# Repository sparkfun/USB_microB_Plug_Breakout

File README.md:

SparkFun USB MicroB Plug Breakout
========================================

[*SparkFun USB MicroB Plug Breakout (BOB-10031)*](https://www.sparkfun.com/products/10031)

We have no idea what USB device you are hooking up to, but if you want to access the microUSB port on something, you might want this. 
We broke out all 5 pins with a vertical microUSB connector for your prototyping needs.

Repository Contents
-------------------

* **/Hardware** - Eagle design files (.brd, .sch)
* **/Production** - Production panel files (.brd)

Documentation
--------------
* **[SparkFun Fritzing repo](https://github.com/sparkfun/Fritzing_Parts)** - Fritzing diagrams for SparkFun products.
* **[SparkFun 3D Model repo](https://github.com/sparkfun/3D_Models)** - 3D models of SparkFun products. 

Version History
---------------
* [v13](https://github.com/sparkfun/USB_microB_Plug_Breakout/v13) - Version 1.3. QC updates to improve manufacturing. Currently live. 
* [v12](https://github.com/sparkfun/USB_microB_Plug_Breakout/v12) - Version 1.2. Retired. 

License Information
-------------------

This product is _**open source**_! 

Please review the LICENSE.md file for license information. 

If you have any questions or concerns on licensing, please contact techsupport@sparkfun.com.

Distributed as-is; no warranty is given.

- Your friends at SparkFun.

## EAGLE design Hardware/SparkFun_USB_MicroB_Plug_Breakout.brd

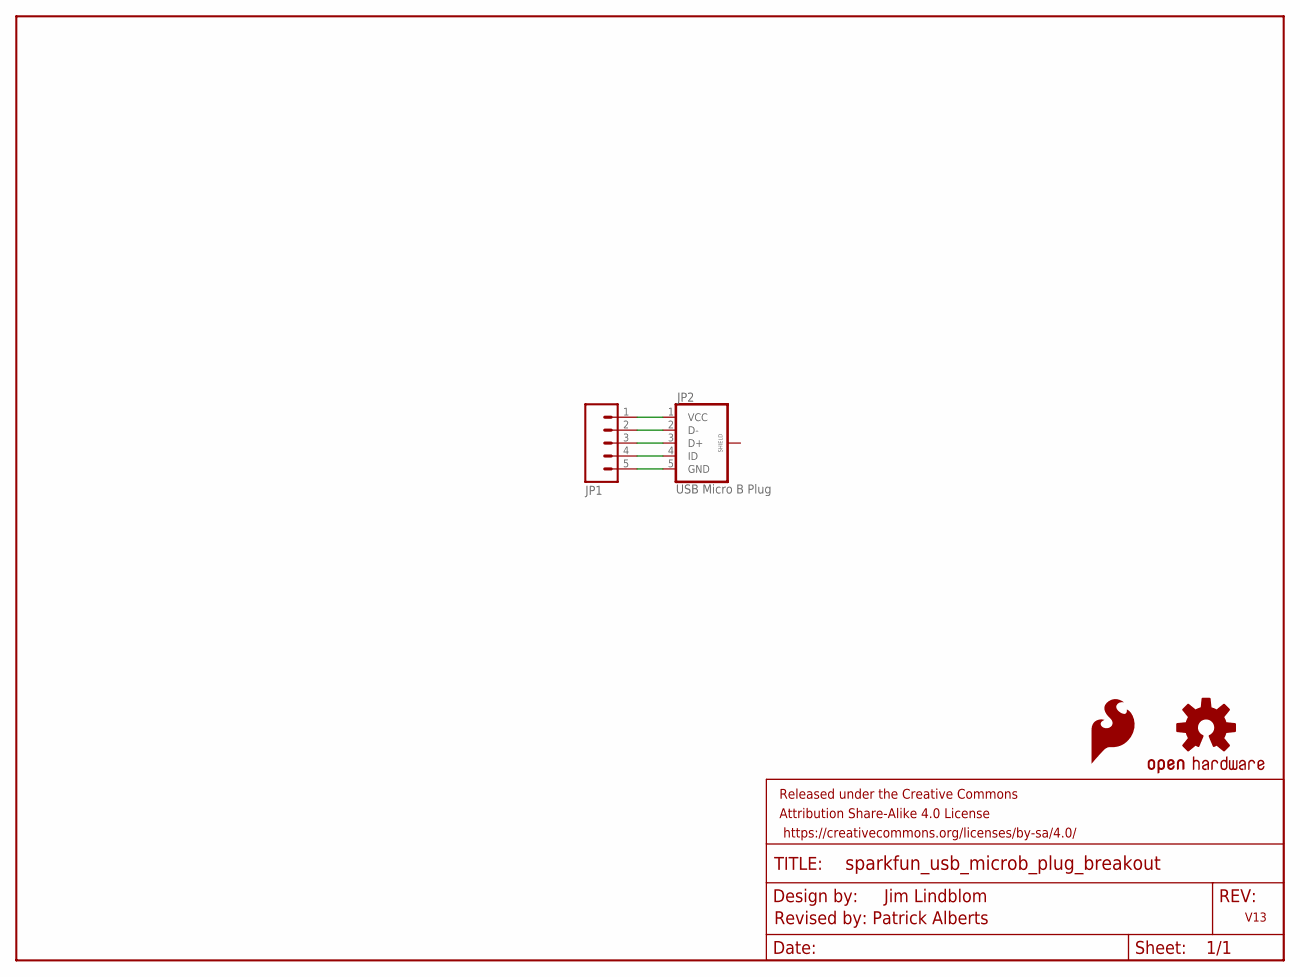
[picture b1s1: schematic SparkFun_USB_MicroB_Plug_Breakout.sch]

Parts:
FRAME1: FRAME-LETTER; CREATIVE_COMMONS
JP1: M05PTH; 1X05
JP2: USB Micro B Plug; MICRO-B-SMT
LOGO1: OSHW-LOGOS; OSHW-LOGO-S
LOGO2: SFE_LOGO_FLAME.1_INCH; SFE_LOGO_FLAME_.1

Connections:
unnamed: JP1.1, JP2.1 (VCC)
unnamed: JP1.2, JP2.2 (D-)
unnamed: JP1.3, JP2.3 (D+)
unnamed: JP1.4, JP2.4 (ID)
unnamed: JP1.5, JP2.5 (GND)

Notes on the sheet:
V13
Revised by: Patrick Alberts
Jim Lindblom

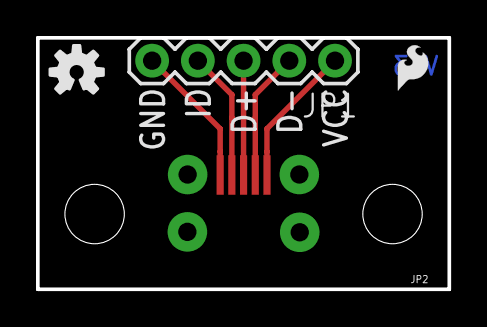
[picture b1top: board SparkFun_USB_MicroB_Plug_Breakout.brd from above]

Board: 2 copper layers, 22.9 x 14.0 mm, 5 parts (0 on the bottom side), 5 nets.

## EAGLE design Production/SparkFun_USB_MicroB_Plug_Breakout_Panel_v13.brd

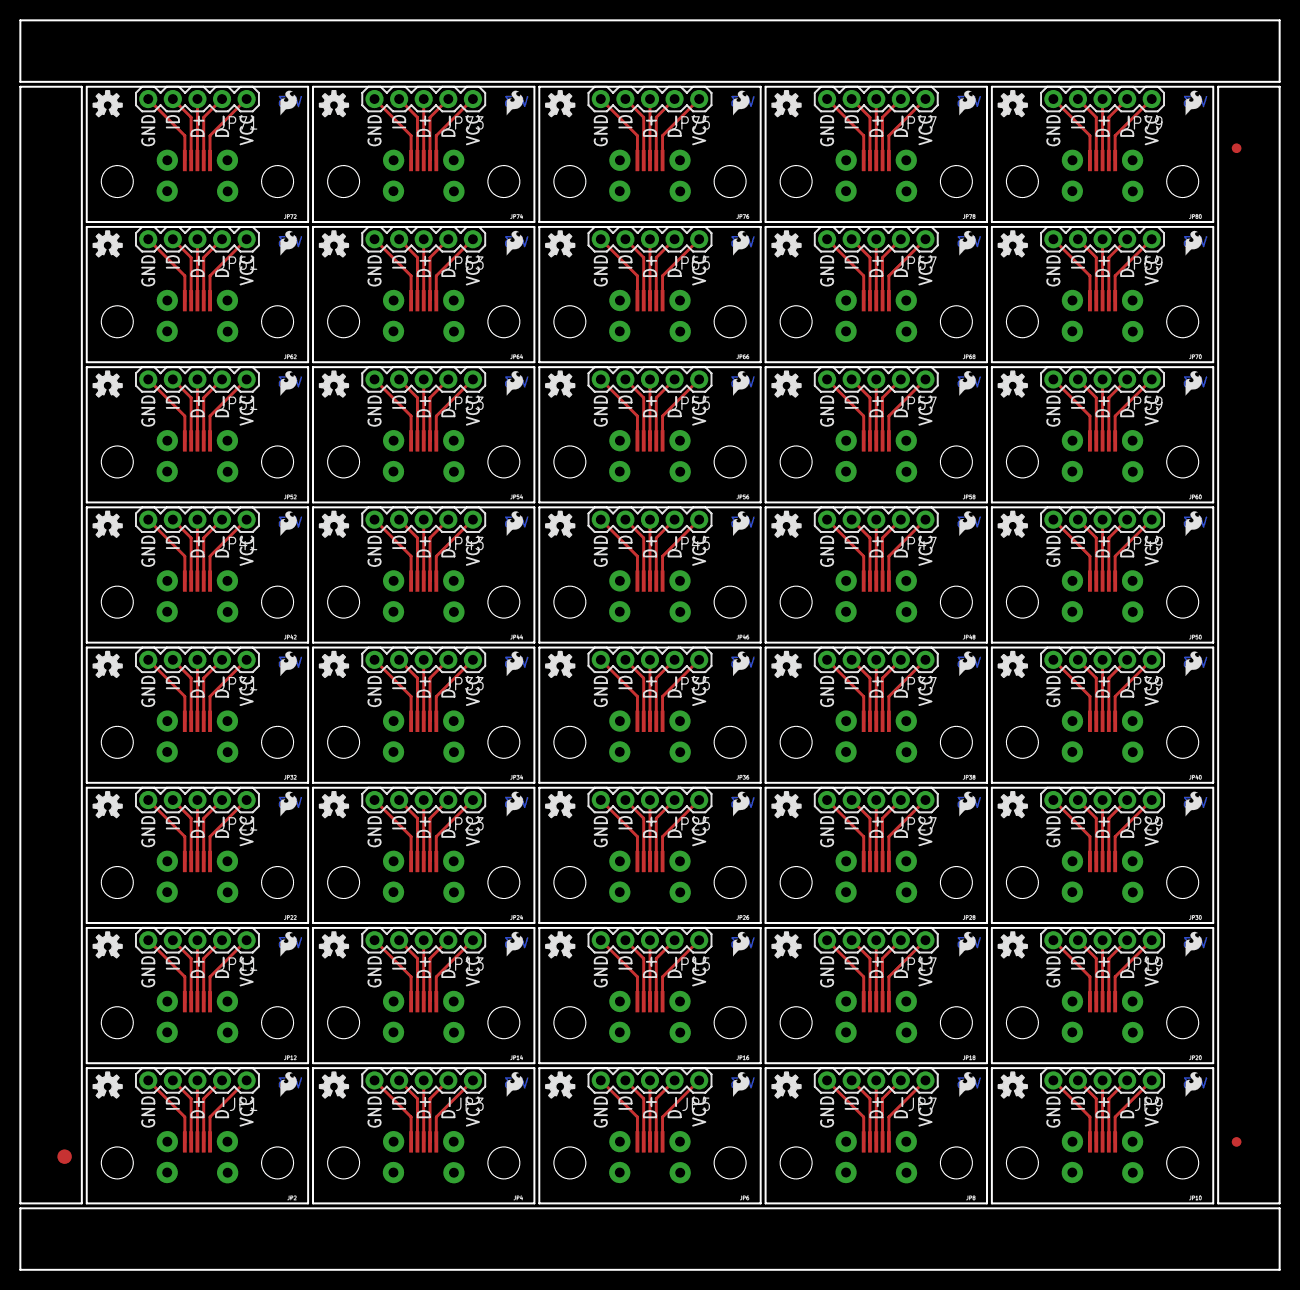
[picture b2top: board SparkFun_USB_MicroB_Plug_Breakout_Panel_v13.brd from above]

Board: 2 copper layers, 130.0 x 129.0 mm, 163 parts (0 on the bottom side), 200 nets.

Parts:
E$1: FIDUCIAL-1.5X3
E$4, E$5: FIDUCIAL-1X2
JP1, JP3, JP5, JP7, JP9, JP11, JP13, JP15, JP17, JP19, JP21, JP23, JP25, JP27, JP29, JP31, JP33, JP35, JP37, JP39, JP41, JP43, JP45, JP47, JP49, JP51, JP53, JP55, JP57, JP59, JP61, JP63, JP65, JP67, JP69, JP71, JP73, JP75, JP77, JP79: 1X05
JP2, JP4, JP6, JP8, JP10, JP12, JP14, JP16, JP18, JP20, JP22, JP24, JP26, JP28, JP30, JP32, JP34, JP36, JP38, JP40, JP42, JP44, JP46, JP48, JP50, JP52, JP54, JP56, JP58, JP60, JP62, JP64, JP66, JP68, JP70, JP72, JP74, JP76, JP78, JP80: USB Micro B Plug; MICRO-B-SMT
LOGO1, LOGO3, LOGO5, LOGO7, LOGO9, LOGO11, LOGO13, LOGO15, LOGO17, LOGO19, LOGO21, LOGO23, LOGO25, LOGO27, LOGO29, LOGO31, LOGO33, LOGO35, LOGO37, LOGO39, LOGO41, LOGO43, LOGO45, LOGO47, LOGO49, LOGO51, LOGO53, LOGO55, LOGO57, LOGO59, LOGO61, LOGO63, LOGO65, LOGO67, LOGO69, LOGO71, LOGO73, LOGO75, LOGO77, LOGO79: OSHW-LOGOS; OSHW-LOGO-S
LOGO2, LOGO4, LOGO6, LOGO8, LOGO10, LOGO12, LOGO14, LOGO16, LOGO18, LOGO20, LOGO22, LOGO24, LOGO26, LOGO28, LOGO30, LOGO32, LOGO34, LOGO36, LOGO38, LOGO40, LOGO42, LOGO44, LOGO46, LOGO48, LOGO50, LOGO52, LOGO54, LOGO56, LOGO58, LOGO60, LOGO62, LOGO64, LOGO66, LOGO68, LOGO70, LOGO72, LOGO74, LOGO76, LOGO78, LOGO80: SFE_LOGO_FLAME.1_INCH; SFE_LOGO_FLAME_.1

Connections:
unnamed: JP1.1, JP2.1
unnamed: JP1.2, JP2.2
unnamed: JP1.3, JP2.3
unnamed: JP1.4, JP2.4
unnamed: JP1.5, JP2.5
unnamed: JP3.1, JP4.1
unnamed: JP3.2, JP4.2
unnamed: JP3.3, JP4.3
unnamed: JP3.4, JP4.4
unnamed: JP3.5, JP4.5
unnamed: JP5.1, JP6.1
unnamed: JP5.2, JP6.2
unnamed: JP5.3, JP6.3
unnamed: JP5.4, JP6.4
unnamed: JP5.5, JP6.5
unnamed: JP7.1, JP8.1
unnamed: JP7.2, JP8.2
unnamed: JP7.3, JP8.3
unnamed: JP7.4, JP8.4
unnamed: JP7.5, JP8.5
unnamed: JP9.1, JP10.1
unnamed: JP9.2, JP10.2
unnamed: JP9.3, JP10.3
unnamed: JP9.4, JP10.4
unnamed: JP9.5, JP10.5
unnamed: JP11.1, JP12.1
unnamed: JP11.2, JP12.2
unnamed: JP11.3, JP12.3
unnamed: JP11.4, JP12.4
unnamed: JP11.5, JP12.5
unnamed: JP13.1, JP14.1
unnamed: JP13.2, JP14.2
unnamed: JP13.3, JP14.3
unnamed: JP13.4, JP14.4
unnamed: JP13.5, JP14.5
unnamed: JP15.1, JP16.1
unnamed: JP15.2, JP16.2
unnamed: JP15.3, JP16.3
unnamed: JP15.4, JP16.4
unnamed: JP15.5, JP16.5
unnamed: JP17.1, JP18.1
unnamed: JP17.2, JP18.2
unnamed: JP17.3, JP18.3
unnamed: JP17.4, JP18.4
unnamed: JP17.5, JP18.5
unnamed: JP19.1, JP20.1
unnamed: JP19.2, JP20.2
unnamed: JP19.3, JP20.3
unnamed: JP19.4, JP20.4
unnamed: JP19.5, JP20.5
unnamed: JP21.1, JP22.1
unnamed: JP21.2, JP22.2
unnamed: JP21.3, JP22.3
unnamed: JP21.4, JP22.4
unnamed: JP21.5, JP22.5
unnamed: JP23.1, JP24.1
unnamed: JP23.2, JP24.2
unnamed: JP23.3, JP24.3
unnamed: JP23.4, JP24.4
unnamed: JP23.5, JP24.5
unnamed: JP25.1, JP26.1
unnamed: JP25.2, JP26.2
unnamed: JP25.3, JP26.3
unnamed: JP25.4, JP26.4
unnamed: JP25.5, JP26.5
unnamed: JP27.1, JP28.1
unnamed: JP27.2, JP28.2
unnamed: JP27.3, JP28.3
unnamed: JP27.4, JP28.4
unnamed: JP27.5, JP28.5
unnamed: JP29.1, JP30.1
unnamed: JP29.2, JP30.2
unnamed: JP29.3, JP30.3
unnamed: JP29.4, JP30.4
unnamed: JP29.5, JP30.5
unnamed: JP31.1, JP32.1
unnamed: JP31.2, JP32.2
unnamed: JP31.3, JP32.3
unnamed: JP31.4, JP32.4
unnamed: JP31.5, JP32.5
unnamed: JP33.1, JP34.1
unnamed: JP33.2, JP34.2
unnamed: JP33.3, JP34.3
unnamed: JP33.4, JP34.4
unnamed: JP33.5, JP34.5
unnamed: JP35.1, JP36.1
unnamed: JP35.2, JP36.2
unnamed: JP35.3, JP36.3
unnamed: JP35.4, JP36.4
unnamed: JP35.5, JP36.5
unnamed: JP37.1, JP38.1
unnamed: JP37.2, JP38.2
unnamed: JP37.3, JP38.3
unnamed: JP37.4, JP38.4
unnamed: JP37.5, JP38.5
unnamed: JP39.1, JP40.1
unnamed: JP39.2, JP40.2
unnamed: JP39.3, JP40.3
unnamed: JP39.4, JP40.4
unnamed: JP39.5, JP40.5
unnamed: JP41.1, JP42.1
unnamed: JP41.2, JP42.2
unnamed: JP41.3, JP42.3
unnamed: JP41.4, JP42.4
unnamed: JP41.5, JP42.5
unnamed: JP43.1, JP44.1
unnamed: JP43.2, JP44.2
unnamed: JP43.3, JP44.3
unnamed: JP43.4, JP44.4
unnamed: JP43.5, JP44.5
unnamed: JP45.1, JP46.1
unnamed: JP45.2, JP46.2
unnamed: JP45.3, JP46.3
unnamed: JP45.4, JP46.4
unnamed: JP45.5, JP46.5
unnamed: JP47.1, JP48.1
unnamed: JP47.2, JP48.2
unnamed: JP47.3, JP48.3
unnamed: JP47.4, JP48.4
unnamed: JP47.5, JP48.5
unnamed: JP49.1, JP50.1
unnamed: JP49.2, JP50.2
unnamed: JP49.3, JP50.3
unnamed: JP49.4, JP50.4
unnamed: JP49.5, JP50.5
unnamed: JP51.1, JP52.1
unnamed: JP51.2, JP52.2
unnamed: JP51.3, JP52.3
unnamed: JP51.4, JP52.4
unnamed: JP51.5, JP52.5
unnamed: JP53.1, JP54.1
unnamed: JP53.2, JP54.2
unnamed: JP53.3, JP54.3
unnamed: JP53.4, JP54.4
unnamed: JP53.5, JP54.5
unnamed: JP55.1, JP56.1
unnamed: JP55.2, JP56.2
unnamed: JP55.3, JP56.3
unnamed: JP55.4, JP56.4
unnamed: JP55.5, JP56.5
unnamed: JP57.1, JP58.1
unnamed: JP57.2, JP58.2
unnamed: JP57.3, JP58.3
unnamed: JP57.4, JP58.4
unnamed: JP57.5, JP58.5
unnamed: JP59.1, JP60.1
unnamed: JP59.2, JP60.2
unnamed: JP59.3, JP60.3
unnamed: JP59.4, JP60.4
unnamed: JP59.5, JP60.5
unnamed: JP61.1, JP62.1
unnamed: JP61.2, JP62.2
unnamed: JP61.3, JP62.3
unnamed: JP61.4, JP62.4
unnamed: JP61.5, JP62.5
unnamed: JP63.1, JP64.1
unnamed: JP63.2, JP64.2
unnamed: JP63.3, JP64.3
unnamed: JP63.4, JP64.4
unnamed: JP63.5, JP64.5
unnamed: JP65.1, JP66.1
unnamed: JP65.2, JP66.2
unnamed: JP65.3, JP66.3
unnamed: JP65.4, JP66.4
unnamed: JP65.5, JP66.5
unnamed: JP67.1, JP68.1
unnamed: JP67.2, JP68.2
unnamed: JP67.3, JP68.3
unnamed: JP67.4, JP68.4
unnamed: JP67.5, JP68.5
unnamed: JP69.1, JP70.1
unnamed: JP69.2, JP70.2
unnamed: JP69.3, JP70.3
unnamed: JP69.4, JP70.4
unnamed: JP69.5, JP70.5
unnamed: JP71.1, JP72.1
unnamed: JP71.2, JP72.2
unnamed: JP71.3, JP72.3
unnamed: JP71.4, JP72.4
unnamed: JP71.5, JP72.5
unnamed: JP73.1, JP74.1
unnamed: JP73.2, JP74.2
unnamed: JP73.3, JP74.3
unnamed: JP73.4, JP74.4
unnamed: JP73.5, JP74.5
unnamed: JP75.1, JP76.1
unnamed: JP75.2, JP76.2
unnamed: JP75.3, JP76.3
unnamed: JP75.4, JP76.4
unnamed: JP75.5, JP76.5
unnamed: JP77.1, JP78.1
unnamed: JP77.2, JP78.2
unnamed: JP77.3, JP78.3
unnamed: JP77.4, JP78.4
unnamed: JP77.5, JP78.5
unnamed: JP79.1, JP80.1
unnamed: JP79.2, JP80.2
unnamed: JP79.3, JP80.3
unnamed: JP79.4, JP80.4
unnamed: JP79.5, JP80.5

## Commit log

2015-05-04 Adding hardware files, updating README
2015-05-04 Fixing typo in README
2015-05-13 Fixed USB Micro footprint. Added OSHW SPK logo
2015-05-28 Added silk and prod attributes.
2015-05-28 Added Measures.
2015-07-06 created panel v13
2015-10-12 updating README, updating license

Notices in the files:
parts and their libraries:
SparkFun-Connectors: Licensing: Creative Commons ShareAlike 4.0 International - https://creativecommons.org/licenses/by-sa/4.0
SparkFun-Aesthetics: Released under the Creative Commons Attribution Share-Alike 4.0 License
SparkFun-Aesthetics: https://creativecommons.org/licenses/by-sa/4.0
